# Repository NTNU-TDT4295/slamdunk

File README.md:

# SLAMdunk

SLAMdunk is a project built to map out environments, using a custom
built PCB shield meant for a Xilinx PYNQ-Z1.

## build

Contains common recipes for building the modules of SLAMdunk
(e.g. makefiles).

## efm32

Code to run MCU on the custom PCB. Functionality includes reading
sensor data from RPLIDAR A1, BNO055, HC-SR04, and communicating over
serial protocols such as UART, I2C and SPI.

## libs

* slamcommon -- Hector SLAM algorithm and common net utilities.
* window -- library for creating X11 windows with OpenGL, and other 3D-rendering utilities.

## pcb

Schematics for the custom PCB shield.

## pynq

General utilities used for deployment to PYNQ. e.g. kernel modules for
Wi-Fi and virtual serial port on USB, and other scripts to get
started.

## pynqslam

The actual SLAMdunk implementation. All functionality related to
running the Hector SLAM algorithm on the PYNQ resides there. This
includes an FPGA implementation of an SPI slave, with double
buffering of the incoming data, as well as the entire implementation
required to run SLAM on a PYNQ. Also contains compiled bit files
needed to deploy to FPGA fabric.

## slamvis

Software running a remote machine for visualizing the output from
pynqslam.

## tools (for fools)

Utilities for testing etc., mainly used in previous iterations of the
system:

* lidar -- visualize the raw output from a LIDAR
* lidar_usb -- receive RPLIDAR output from USB
* pointcloud -- legacy program for visualizing 3D pointclouds
* simulator -- legacy program for simulating LIDAR data
* slam -- alternative implementation of pynqslam for running on non-PYNQ machine

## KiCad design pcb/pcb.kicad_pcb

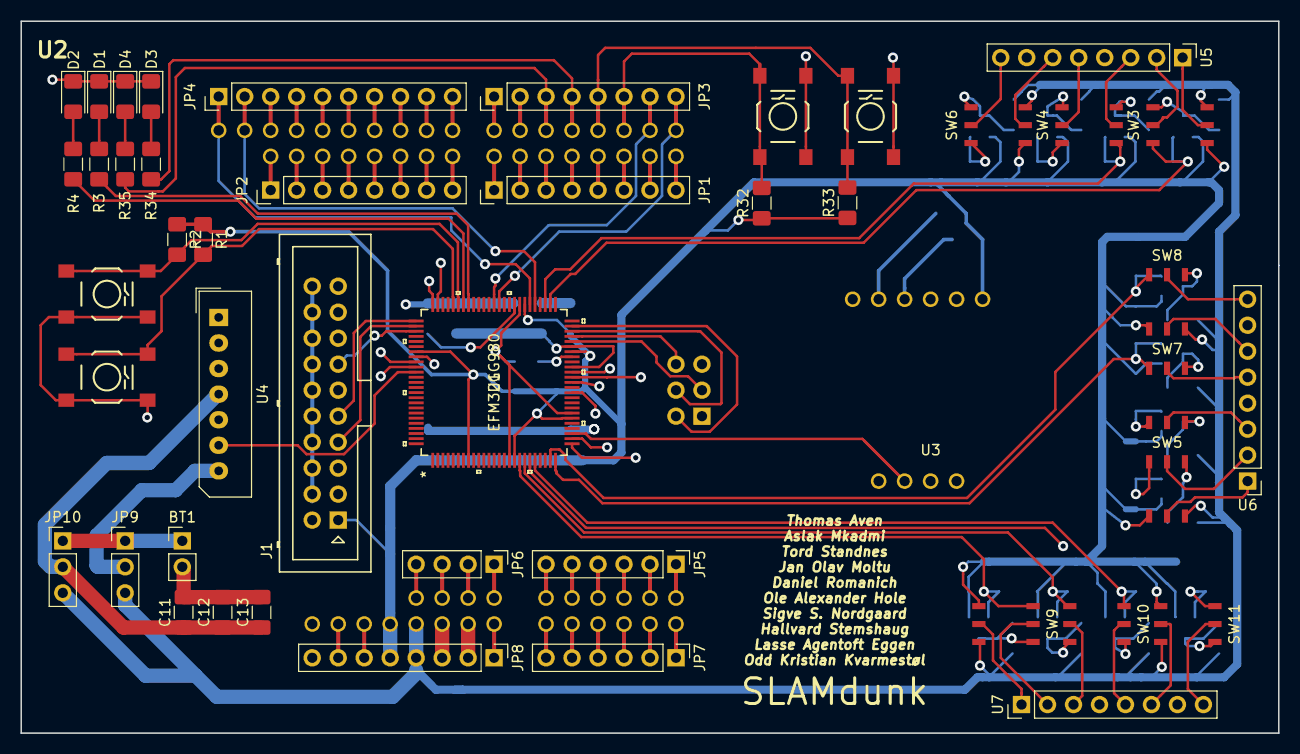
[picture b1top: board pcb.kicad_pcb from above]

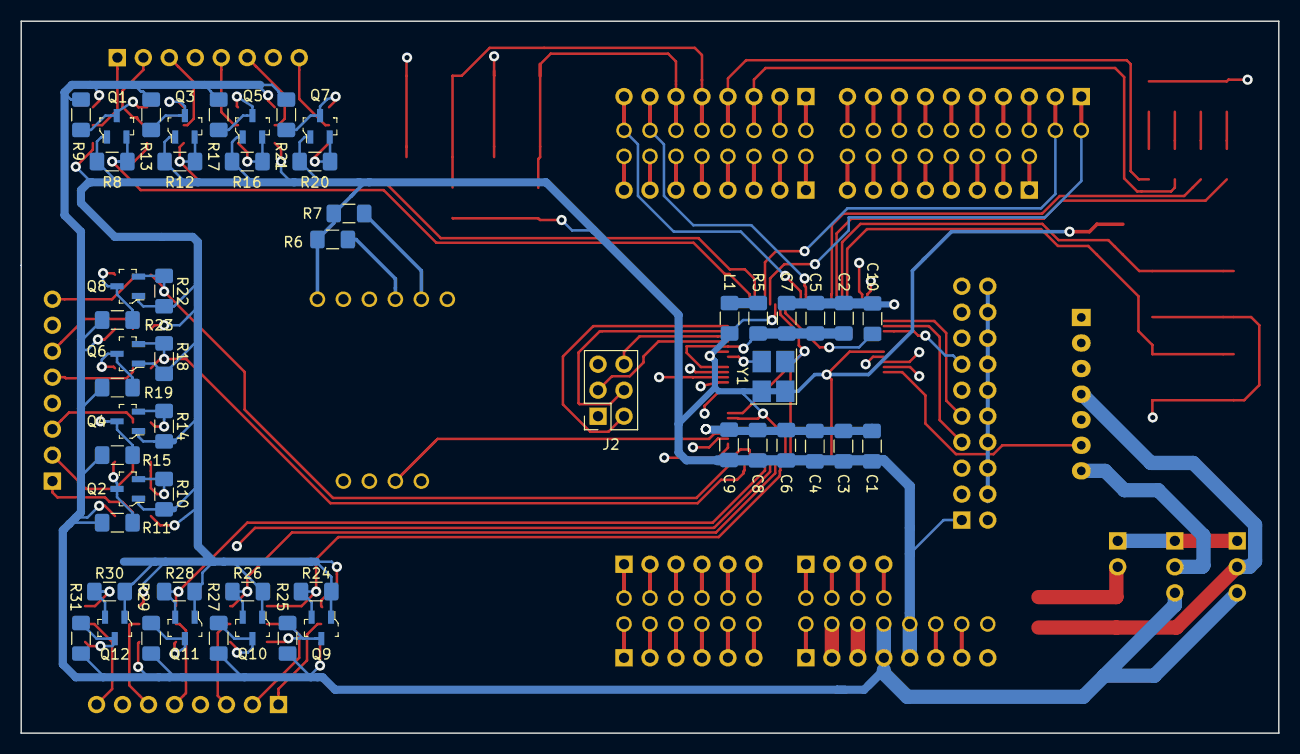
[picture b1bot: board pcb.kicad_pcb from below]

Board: 4 copper layers, 122.9 x 69.6 mm, 99 parts (52 on the bottom side), 128 nets.

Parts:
BT1: Battery; PinHeader_1x02_P2.54mm_Vertical
C1, C3, C4, C6, C8: 100n; C_1206_3216Metric_Pad1.42x1.75mm_HandSolder
C2, C5: 10nF; C_1206_3216Metric_Pad1.42x1.75mm_HandSolder
C7, C10: 1uF; C_1206_3216Metric_Pad1.42x1.75mm_HandSolder
C9: 10u; C_1206_3216Metric_Pad1.42x1.75mm_HandSolder
C11: 10μF; C_1206_3216Metric_Pad1.42x1.75mm_HandSolder
C12: 1μF; C_1206_3216Metric_Pad1.42x1.75mm_HandSolder
C13: 100nF; C_1206_3216Metric_Pad1.42x1.75mm_HandSolder
D1, D2, D3, D4: LED; LED_1206_3216Metric_Pad1.42x1.75mm_HandSolder
J1: Conn_02x10_Odd_Even; Multicomp_MC9A12-2034_2x10_P2.54mm_Vertical
J2: Conn_02x03_Counter_Clockwise; PinSocket_2x03_P2.54mm_Vertical
JP1, JP2, JP3, JP8: M08; PinHeader_1x08_P2.54mm_Vertical
JP4: M10; PinHeader_1x10_P2.54mm_Vertical
JP5, JP7: M06; PinHeader_1x06_P2.54mm_Vertical
JP6: M04; PinHeader_1x04_P2.54mm_Vertical
JP9, JP10: Jumper_NC_Dual; PinHeader_1x03_P2.54mm_Vertical
L1: 742792662; L_1206_3216Metric_Pad1.42x1.75mm_HandSolder
Q1, Q2, Q3, Q4, Q5, Q6, Q7, Q8, Q9, Q10, Q11, Q12: BSS138; SOT-23-3
R1, R2, R3, R4, R32, R33, R34, R35: R; R_1206_3216Metric_Pad1.42x1.75mm_HandSolder
R5: 1; R_1206_3216Metric_Pad1.42x1.75mm_HandSolder
R6: 2.2k; R_1206_3216Metric_Pad1.42x1.75mm_HandSolder
R7: 4.7k; R_1206_3216Metric_Pad1.42x1.75mm_HandSolder
R8, R9, R10, R11, R12, R13, R14, R15, R16, R17, R18, R19, R20, R21, R22, R23, R24, R25, R26, R27, R28, R29, R30, R31: 10k; R_1206_3216Metric_Pad1.42x1.75mm_HandSolder
SW1, SW2, SW12, SW13: SW_PUSHBUTTON; SW_PUSHBUTTON_SMD
SW3, SW4, SW5, SW6, SW7, SW8, SW9, SW10, SW11: SW_2xSPDT; CAS-D20TB
U1: EFM32GG980
U2: ARDUINO_PYNQ_SHIELD
U3: IMU; BNO055
U4: lidar; Molex_SPOX_5267-07A_1x07_P2.50mm_Vertical
U5, U6, U7: ULTRASONIC-GPIO; PinHeader_1x08_P2.54mm_Vertical
Y1: Crystal_GND23; Crystal_SMD_3225-4Pin_3.2x2.5mm_HandSoldering

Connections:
+3V3: C1.1, C3.1, C4.1, C6.1, C8.1, C9.1, J1.1, JP8.5, L1.1, Q1.1, Q2.1, Q3.1, Q4.1, Q5.1, Q6.1, Q7.1, Q8.1, Q9.1, Q10.1, Q11.1, Q12.1, R1.1, R2.1, R6.1, R7.1, R8.1, R10.1, R12.1, R14.1, R16.1, R18.1, R20.1, R22.1, R24.1, R26.1, R28.1, R30.1, R32.1, R33.1, SW3.3, SW5.3, SW6.3, SW8.3, SW9.3, SW11.3, U1.8, U1.17, U1.31, U1.44, U1.57, U1.82, U2.3V3, U3.6, Y1.1, Y1.4
/AVDD_DEC: C2.1, C5.1, C7.1, R5.2, U1.41, U1.45
/CLOCK/HFXTAL_N: U1.43, Y1.3
/DEC: C10.2, U1.59
/EFM_DEBUG/LED_1: R3.1, U1.68
/EFM_DEBUG/LED_2: R4.1, U1.69
/EFM_DEBUG/SW_1: R1.2, SW1.1, U1.71
/EFM_DEBUG/SW_2: R2.2, SW2.1, U1.70
/JTAG/SWCLK: J1.9, U1.76
/JTAG/SWDIO: J1.7, U1.77
/JTAG/SWO: J1.13, U1.78
/LIDAR/MOTO_CTRL: U1.86, U4.6
/LIDAR/RX: U1.85, U4.3
/LIDAR/TX: U1.84, U4.2
/MCU_RST: J1.15, U1.36
/PA7_C1: Q2.2, R10.2, SW5.6, U1.26
/PA8_C2: Q4.2, R14.2, SW7.3, U1.27
/PA9_IMU_INT: U1.28, U3.9
/PB7_CTX: Q8.2, R22.2, SW8.6, U1.24
/PB8_CRX: Q6.2, R18.2, SW7.6, U1.25
/PB10_IMU_RST: U1.38, U3.1
/PB11_IMU_SDA: R6.2, U1.39, U3.3
/PB12_IMU_SCL: R7.2, U1.40, U3.2
/PC0_B1: Q9.2, R24.2, SW9.6, U1.18
/PC1_B2: Q10.2, R26.2, SW10.3, U1.19
/PC2_BTX: Q12.2, R30.2, SW11.6, U1.20
/PC3_BRX: Q11.2, R28.2, SW10.6, U1.21
/PD6_A1: Q1.2, R8.2, SW3.6, U1.52
/PD7_A2: Q3.2, R12.2, SW4.3, U1.53
/PF10_ATX: Q7.2, R20.2, SW6.6, U1.74
/PF11_ARX: Q5.2, R16.2, SW4.6, U1.75
/PYNQ-DEBUG/LED_1: JP3.4, R34.1, U2.4
/PYNQ-DEBUG/LED_2: JP3.3, R35.1, U2.5
/PYNQ-DEBUG/SW_1: JP3.6, R32.2, SW12.1, U2.2
/PYNQ-DEBUG/SW_2: JP3.5, R33.2, SW13.1, U2.3
/PYNQ_RX: JP3.8, U1.62, U2.0
/PYNQ_SCL: JP4.1, U1.56, U2.SCL
/PYNQ_SDA: JP4.2, U1.55, U2.SDA
/PYNQ_TX: JP3.7, U1.63, U2.1
/SPI/MISO: J2.6, U1.47
/SPI/MOSI: J2.3, U1.46
/SPI/SCLK: J2.4, U1.48
/SPI/SS: J2.2, U1.49
GND: BT1.2, C1.2, C2.2, C3.2, C4.2, C5.2, C6.2, C7.2, C8.2, C9.2, C10.1, C11.2, C12.2, C13.2, D1.1, D2.1, D3.1, D4.1, J1.4, J1.6, J1.8, J1.10, J1.12, J1.14, J1.16, J1.18, J1.20, JP8.2, JP8.3, SW1.2, SW2.2, SW12.2, SW13.2, U1.16, U1.32, U1.58, U1.83, U2.GND1, U2.GND2, U3.4, U4.1, U4.5, U5.4, U5.7, U6.4, U6.7, U7.4, U7.7, Y1.2
unnamed: BT1.1, JP9.1, JP10.1
unnamed: C11.1, C12.1, C13.1, JP10.2, U4.4
unnamed: D1.2, R3.2
unnamed: D2.2, R4.2
unnamed: D3.2, R34.2
unnamed: D4.2, R35.2
unnamed: JP1.1, U2.33
unnamed: JP1.2, U2.32
unnamed: JP1.3, U2.31
unnamed: JP1.4, U2.30
unnamed: JP1.5, U2.29
unnamed: JP1.6, U2.28
unnamed: JP1.7, U2.27
unnamed: JP1.8, U2.26
unnamed: JP2.1, U2.41
unnamed: JP2.2, U2.40
unnamed: JP2.3, U2.39
unnamed: JP2.4, U2.38
unnamed: JP2.5, U2.37
unnamed: JP2.6, U2.36
unnamed: JP2.7, U2.35
unnamed: JP2.8, U2.34
unnamed: JP3.1, U2.7
unnamed: JP3.2, U2.6
unnamed: JP4.3, U2.A_R
unnamed: JP4.4, U2.G
unnamed: JP4.5, U2.13
unnamed: JP4.6, U2.12
unnamed: JP4.7, U2.11
unnamed: JP4.8, U2.10
unnamed: JP4.9, U2.9
unnamed: JP4.10, U2.8
unnamed: JP5.1, U2.A11
unnamed: JP5.2, U2.A10
unnamed: JP5.3, U2.A9
unnamed: JP5.4, U2.A8
unnamed: JP5.5, U2.A7
unnamed: JP5.6, U2.A6
unnamed: JP6.1, U2.XV_R
unnamed: JP6.2, U2.XGND
unnamed: JP6.3, U2.V_N
unnamed: JP6.4, U2.V_P
unnamed: JP7.1, U2.A5
unnamed: JP7.2, U2.A4
unnamed: JP7.3, U2.A3
unnamed: JP7.4, U2.A2
unnamed: JP7.5, U2.A1
unnamed: JP7.6, U2.A0
unnamed: JP8.1, U2.VIN
unnamed: JP8.6, U2.RST
unnamed: JP8.7, U2.IO_R
unnamed: JP9.2, U4.7
unnamed: L1.2, R5.1
unnamed: Q1.3, R9.2, SW3.4
unnamed: Q2.3, R11.2, SW5.4
unnamed: Q3.3, R13.2, SW4.1
unnamed: Q4.3, R15.2, SW7.1
unnamed: Q5.3, R17.2, SW4.4
unnamed: Q6.3, R19.2, SW7.4
unnamed: Q7.3, R21.2, SW6.4
unnamed: Q8.3, R23.2, SW8.4
unnamed: Q9.3, R25.2, SW9.4
unnamed: Q10.3, R27.2, SW10.1
unnamed: Q11.3, R29.2, SW10.4
unnamed: Q12.3, R31.2, SW11.4
unnamed: SW3.2, U5.1
unnamed: SW3.5, U5.2
unnamed: SW4.2, U5.3
unnamed: SW4.5, U5.5
unnamed: SW5.2, U6.1
unnamed: SW5.5, U6.2
unnamed: SW6.2, U5.6
unnamed: SW6.5, U5.8
unnamed: SW7.2, U6.3
unnamed: SW7.5, U6.5
unnamed: SW8.2, U6.6
unnamed: SW8.5, U6.8
unnamed: SW9.2, U7.1
unnamed: SW9.5, U7.2
unnamed: SW10.2, U7.3
unnamed: SW10.5, U7.5
unnamed: SW11.2, U7.6
unnamed: SW11.5, U7.8
VCC: JP8.4, JP9.3, JP10.3, R9.1, R11.1, R13.1, R15.1, R17.1, R19.1, R21.1, R23.1, R25.1, R27.1, R29.1, R31.1, SW3.1, SW5.1, SW6.1, SW8.1, SW9.1, SW11.1, U2.5V

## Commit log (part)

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2018-09-05 Create an inital test to run on the PYNQ FPGA -- works.
2018-09-05 Use CFFI within Python to interface with FPGA.
2018-09-05 Make deployment a little bit smoother.
2018-09-05 Create awful Makefile to get started with execution on PYNQ.
2018-09-05 Implement DRAM-routines to access DRAM from Python.
2018-09-06 Attempt accessing BRAM with Yaman's example -- doesnt work for now.
2018-09-06 Use an accelerator to move memory in DRAM with DMA (streams).
2018-09-06 Remove previous testing that is no longer needed.
2018-09-06 Reading/setting BRAM can now be done from Python.
2018-09-06 Clean up unneeded stuff; it should be possible to do some actual work now.
2018-09-08 Add what's needed from Gecko_SDK to write code for STK3700.
2018-09-08 Add some UART modules, including a few things QBART used last year.
2018-09-10 organize source files
2018-09-12 update bsp STK
2018-09-12 Add LCD STK and refactor
2018-09-12 Add GPIO interrupts
2018-09-12 add a unimpressive clock
2018-09-12 Successfully send some data over UART (i.e. uncomment IRQ-handler..).
2018-09-13 Reorganize header and source files.
2018-09-13 Add seconds to clock
2018-09-13 Add missing stdio header, and update serial.h correctly.
2018-09-13 Change baud rate to 115200, and location to PB{9,10} for UART.
2018-09-13 Make clock asynchronous
2018-09-13 Write UART input to LCD screen.
2018-09-13 Slight refactor of serial. Declare func to silence compile warning.
2018-09-13 Enable UART0 so it works to speak to the chip on two channels.
2018-09-14 add i2c driver
2018-09-14 I2C, scaffold and initial test.
2018-09-15 Successfully check the system status of the BNO055 and start set IMU mode.
2018-09-15 Fetch some euler angles, only works for a little bit before crashing the EFM32.
2018-09-15 Only fetch the x-dir euler angle, as this doesnt seem to crash the EFM32.
2018-09-16 Move up and down with camera pitch
2018-09-16 Fix keyboard keys getting stuck on key repeat
2018-09-16 Factor out platform-agnostic code from main
2018-09-17 Implement rendering octree
2018-09-18 Implement loading points from obj files, and toggle octree boundaries
2018-09-18 Split out camera code
2018-09-18 Add PCB project
2018-09-18 Add gitignore
2018-09-18 Add symbols for EFM32, IMU and sonars
2018-09-18 Add simulator
2018-09-18 Readd submodules for glm and glad
2018-09-18 Fetch/set arbitrary registers from BNO055 (e.g. quaternions).
2018-09-18 Clean up serial.{c,h} after debugging detour.
2018-09-18 Make I2C independent from own BNO055 module.
2018-09-18 Refactor fetching euler samples, and use a simple example to display pitch.
2018-09-18 Add linear acceleration -- it's harder to debug on the LCD.
2018-09-19 Add EFM32GG980 library
2018-09-19 Create fairly simple driver for HC-SR04.
2018-09-20 Add first draft of pcb
2018-09-20 Change clock pin
2018-09-20 Persist obj vertex data
2018-09-20 Add 'sensor ball' to simulator
2018-09-20 Implement drawing rays from the sensor
2018-09-20 Ignore synthesis generated files.
2018-09-20 Simple UART circuit. Mostly relevant for general GPIO setup.
2018-09-21 Make overflow of TIMER0 the time out of HC-SR04.
2018-09-21 Make uartPutChar take an UART channel as input.
2018-09-21 Also transfer IMU status on UART channel 1 (to PYNQ).
2018-09-21 Implement sending and receiving point cloud data
2018-09-21 Added sample test for UART. UART passthrough. (GPIO passthrough).
2018-09-21 Fix mouse grab on window focus loss
2018-09-21 Implement rotation of sensor
2018-09-21 Fetch quaternion data and send it to PYNQ over UART.
2018-09-21 Fixed rotation input into simulator
2018-09-21 Add test reflector of IMU data from PYNQ.
2018-09-21 added raycasting
2018-09-23 Integrate ray intersection alorithm into simulator
2018-09-23 Use retry interval to reconnect PYNQ to remote pointcloud.
2018-09-23 Attempt initializing interrupts from IMU movement (doesn't work yet).
2018-09-23 Update make script to do incremental builds
2018-09-23 Invert quaternion values to seemingly fit the expected rotations (hack, wat)
2018-09-23 Try reconnecting reflector after ConnectionResetError.
2018-09-23 Use int16_t for IMU values and send them without delay.
2018-09-23 Add script for plotting accelerometer data from the pynq
2018-09-24 Implement axis in point cloud visualizer
2018-09-25 lagt til SPI
2018-09-25 Added levelswitch
2018-09-26 Prettyfy Schematic
2018-09-26 Add PYNQ debug pins
2018-09-26 Finishe schematic, add netlist and start editing pcb design
2018-09-26 start on pcb layout
2018-09-27 Add IMU footprint
2018-09-27 continue on pcb
2018-09-28 Add level shifters and jumpers and new gpio
2018-10-01 Think it is somewhat finished
2018-10-02 Initial SPI curcuit.
2018-10-02 myInstFxn = SPI_Slave()
2018-10-02 Div. SPI stuff. Scaffolding for PYNQ and EFM32GG.
2018-10-02 Add BNO055 footprint
2018-10-02 remove extra footprint
2018-10-02 fix library
2018-10-02 Some small fixes and gerber files
2018-10-03 Lidar initialization
2018-10-03 More lidar headers
2018-10-03 Fix pin silk and size of IMU
2018-10-03 Fix design rules
2018-10-03 Fetch and forward rotation data from Lidar over UART.
2018-10-03 SPI for EFM ready for testing. Debug LEDs for PYNQ SPI.
2018-10-03 Send a start byte and theta + distance from LIDAR to UART output.
2018-10-03 Implement lidar output visualizer
2018-10-04 PoC SPI efm->efm.
2018-10-07 SPI master->slave: efm32gg->PYNQ.
2018-10-07 Don't continuously send LIDAR data.
2018-10-07 Make LIDAR code a bit more self contained.
2018-10-07 Make it simpler to output LIDAR samples.
2018-10-07 Each LIDAR sample is 5 bytes.
2018-10-07 Implement sending data readings to the lidar visualizer from the simulator
2018-10-07 Allow not capturing the mouse
2018-10-08 Clean up slightly, add interleaving of IMU-data.
2018-10-08 Actually pass IMU data along with LIDAR data.
    For later: the breadboard seems to not work as expected when you wish
    to move the LIDAR. This may result in very painful debugging sessions.
2018-10-08 Print values reflected by test_serial to pointcloud.
2018-10-16 catkin_ws contains the source code needed to build and deploy hector_SLAM in ROS
2018-10-17 Add hector slam
2018-10-17 Factor out lidar input
2018-10-18 Implement visualisation of occupancy grid
2018-10-18 Begin reimplementing hector_slam_lib imperatively
2018-10-18 Replace Eigen with glm
2018-10-19 Wifi config.
2018-10-19 add kernel module for wifi driver
2018-10-19 Fix some issue in hector slam implementation and add visalization of mipmapped occ grids
2018-10-19 Replace submodules with actoal repos
2018-10-19 Reverse matrix multiplication order
2018-10-20 Fix some more issues with hector slam
2018-10-20 Factor out HectorSlamProcessor class
2018-10-21 Factor out MapRepMultiMap
2018-10-21 Factor out MapProcContainer
2018-10-21 Factor out ScanMatcher
2018-10-21 Factor out OccGridMapUtil
2018-10-21 Factor out GridMap
2018-10-21 Pull out relevant functions from UtilFunctions
2018-10-21 Replace DataContainer with plain array
2018-10-21 Clean up after refactor
2018-10-21 Precalculate map to world and world to map matrices
2018-10-21 made the makefile ubuntu friendly
2018-10-22 removed cat_kin_ws, obsolete implementation of hector_slam through ROS
2018-10-22 Invariant SPI config.
2018-10-22 SPI for PYNQ. SPI header pins.
2018-10-22 Remove old hector slam lib
2018-10-22 Add test lidar reading application
2018-10-22 SPI basic chisel peek/poke test.
2018-10-22 Efm and pynq SPI conformance. Testable setup.
2018-10-23 Implement visulaizer
2018-10-23 Add script for dynamic ssh to the pynq
2018-10-23 SPI -> 32 bit 2048 addr bram buffer.
2018-10-23 EFM SPI test setup. Alphabet 500 kHz.
2018-10-24 PoC Lidar data on SPI BRAM
2018-10-24 Checkpoint SPI (Charlie).
2018-10-24 Checkpoint for PoC LIDAR -> SPI.
2018-10-24 Itty bitty change for PoC to properly read all LIDAR data.
2018-10-24 Compare first and last word to real data.
2018-10-25 Continuously send LIDAR data from EFM.
2018-10-25 script to automatically setup ethernet on the pynq
2018-10-25 also setup wifi driver
2018-10-25 Integrating projects. FPGA driver base.
2018-10-25 Auto: build, load bitfile, run rosetta.
2018-10-26 Move common things into slam_common
2018-10-26 Enable lidar motor GPIO pin
2018-10-26 remove hardcoding of uart channels in lidar.
2018-10-26 Reflect SPI header moved to sd pins.
2018-10-27 UART device and location EFM@pcb pinout
2018-10-27 SPI @pcb modded pins.
2018-10-28 Implement tiled map transfer
2018-10-28 Add readme
2018-10-28 Implement visualizing the current position of the lidar
2018-10-28 Implement sending pose
2018-10-28 Fix issues related to tile transfer.
    Implicit types in C/C++ can be a pain... (1 << 64) returns a 32-bit number.
2018-10-28 Avoid program crash on connection loss in slam
2018-10-28 Implement visualizing the path traveled by the lidar
2018-10-29 Move slamvis net functions to slam_common
2018-10-29 add wifi setup
2018-10-29 why not init both channels..
2018-10-30 Toggle lidar button efm32gg.
2018-10-30 Send data over eth to visualizer.
2018-10-30 Refactoring :construction_worker:
2018-10-30 Formatting...
2018-10-30 Reset button for FPGA SPI buffers. For lidar sync.
2018-10-30 Send data over SPI, no UART debug.
2018-10-30 IMU I2C setup for PCB layout.
2018-10-30 Implement reset path
2018-10-30 Remove glm doc
2018-11-01 Network pynq->slam w/retry connection.
2018-11-01 Slam :wrench: integrated on pynq. :hammer:
2018-11-01 autosetup new password on pynq
2018-11-01 Added option for timing parts of hector_slam.
2018-11-02 Update deployment of pynqslam/slam_common.
2018-11-02 Cleanup SPI chisel.
2018-11-02 C-c - SIGINT wait for full buffer.
2018-11-02 Send only complete revolutions of calculated data.
2018-11-02 Ensure slam_vis reads all the requested data
    Sometimes recv would not read all the data was requested, which caused future
    packets to be misread.
2018-11-02 Unmagic them constants.
2018-11-02 Move rosetta generator.
2018-11-02 Add stable bitfile.
2018-11-02 Create Makefile path var for develop bitfile. Ignore develop.bit.
2018-11-02 Fix missing offset when receiving packet data in multiple parts
2018-11-02 Implement hector slam clear and free
2018-11-02 Fix typo in makefile flags
2018-11-03 Update EFM32 main.c with current stable behaviour.
2018-11-03 Remove unused leds.{c,h}.
2018-11-03 Start removing unused LCD code.
2018-11-03 Move interrupt.{c,h} to just gpio.{c,h}.
2018-11-03 BNO055 -> IMU, and remove some unused stuff.
2018-11-03 Remove some unused stuff from LIDAR interfacing.
2018-11-03 Remove unused I2C code.
2018-11-03 Chomp unused LCD files.
2018-11-03 Move gpiointerrupt to vendor directory.
2018-11-03 Remove a bunch of used lib/ header files.
2018-11-03 Comment out sonar callback (false unused positives).
2018-11-03 Implement a new project structure
2018-11-03 Remove uneeded .gitmodules.
2018-11-03 Add string.h and fix warnings.
2018-11-03 Add .gitignores.
2018-11-03 Fix linking problem with -lcma order.
2018-11-03 Implement deployment from root of slamdunk.
2018-11-03 Add README for root of project.
2018-11-03 Add images to README.md.
2018-11-03 Add systemd service for pynqslam
2018-11-03 Implement run and stop pynqslam on remote pynq
2018-11-03 Allow specifying IP-address of slamvis host when running
2018-11-05 Fix several small building errors.
2018-11-05 Improve deployment (systemd, sudoers).
2018-11-05 Implement loading bitfile using systemd
2018-11-05 Add .gittattributes linguist-ignore vendor code.
2018-11-06 Add superfluous make rule for restart.
2018-11-06 Change update cutoff to 80.
2018-11-06 Add new visualizer image for README.
2018-11-06 Update setup image in README.
2018-11-06 Fix disconnection bug and lower update cutoff.
2018-11-06 fix some problems in setup script
2018-11-06 Implement target flag for compiling for pynq
2018-11-07 Rewrite SPI, add preprocessing.
2018-11-08 Added (possibly working) cordic module
2018-11-16 Fix aspect ratio of slamvis
2018-11-16 Fix the red indicator not being scaled properly
2018-11-16 Fix float-overflow bug in hector slam
    At some point, the hector slam algorithm might get stuck at NaN, because exp of
    the map value becomes too big. This was resolved by capping the map values to
    50.0f.
2018-11-16 Implement visualising real-time lidar data
2018-11-17 Update the example image

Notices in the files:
parts and their libraries:
Copyright 2016 Accelerated Designs. All rights reserved.
